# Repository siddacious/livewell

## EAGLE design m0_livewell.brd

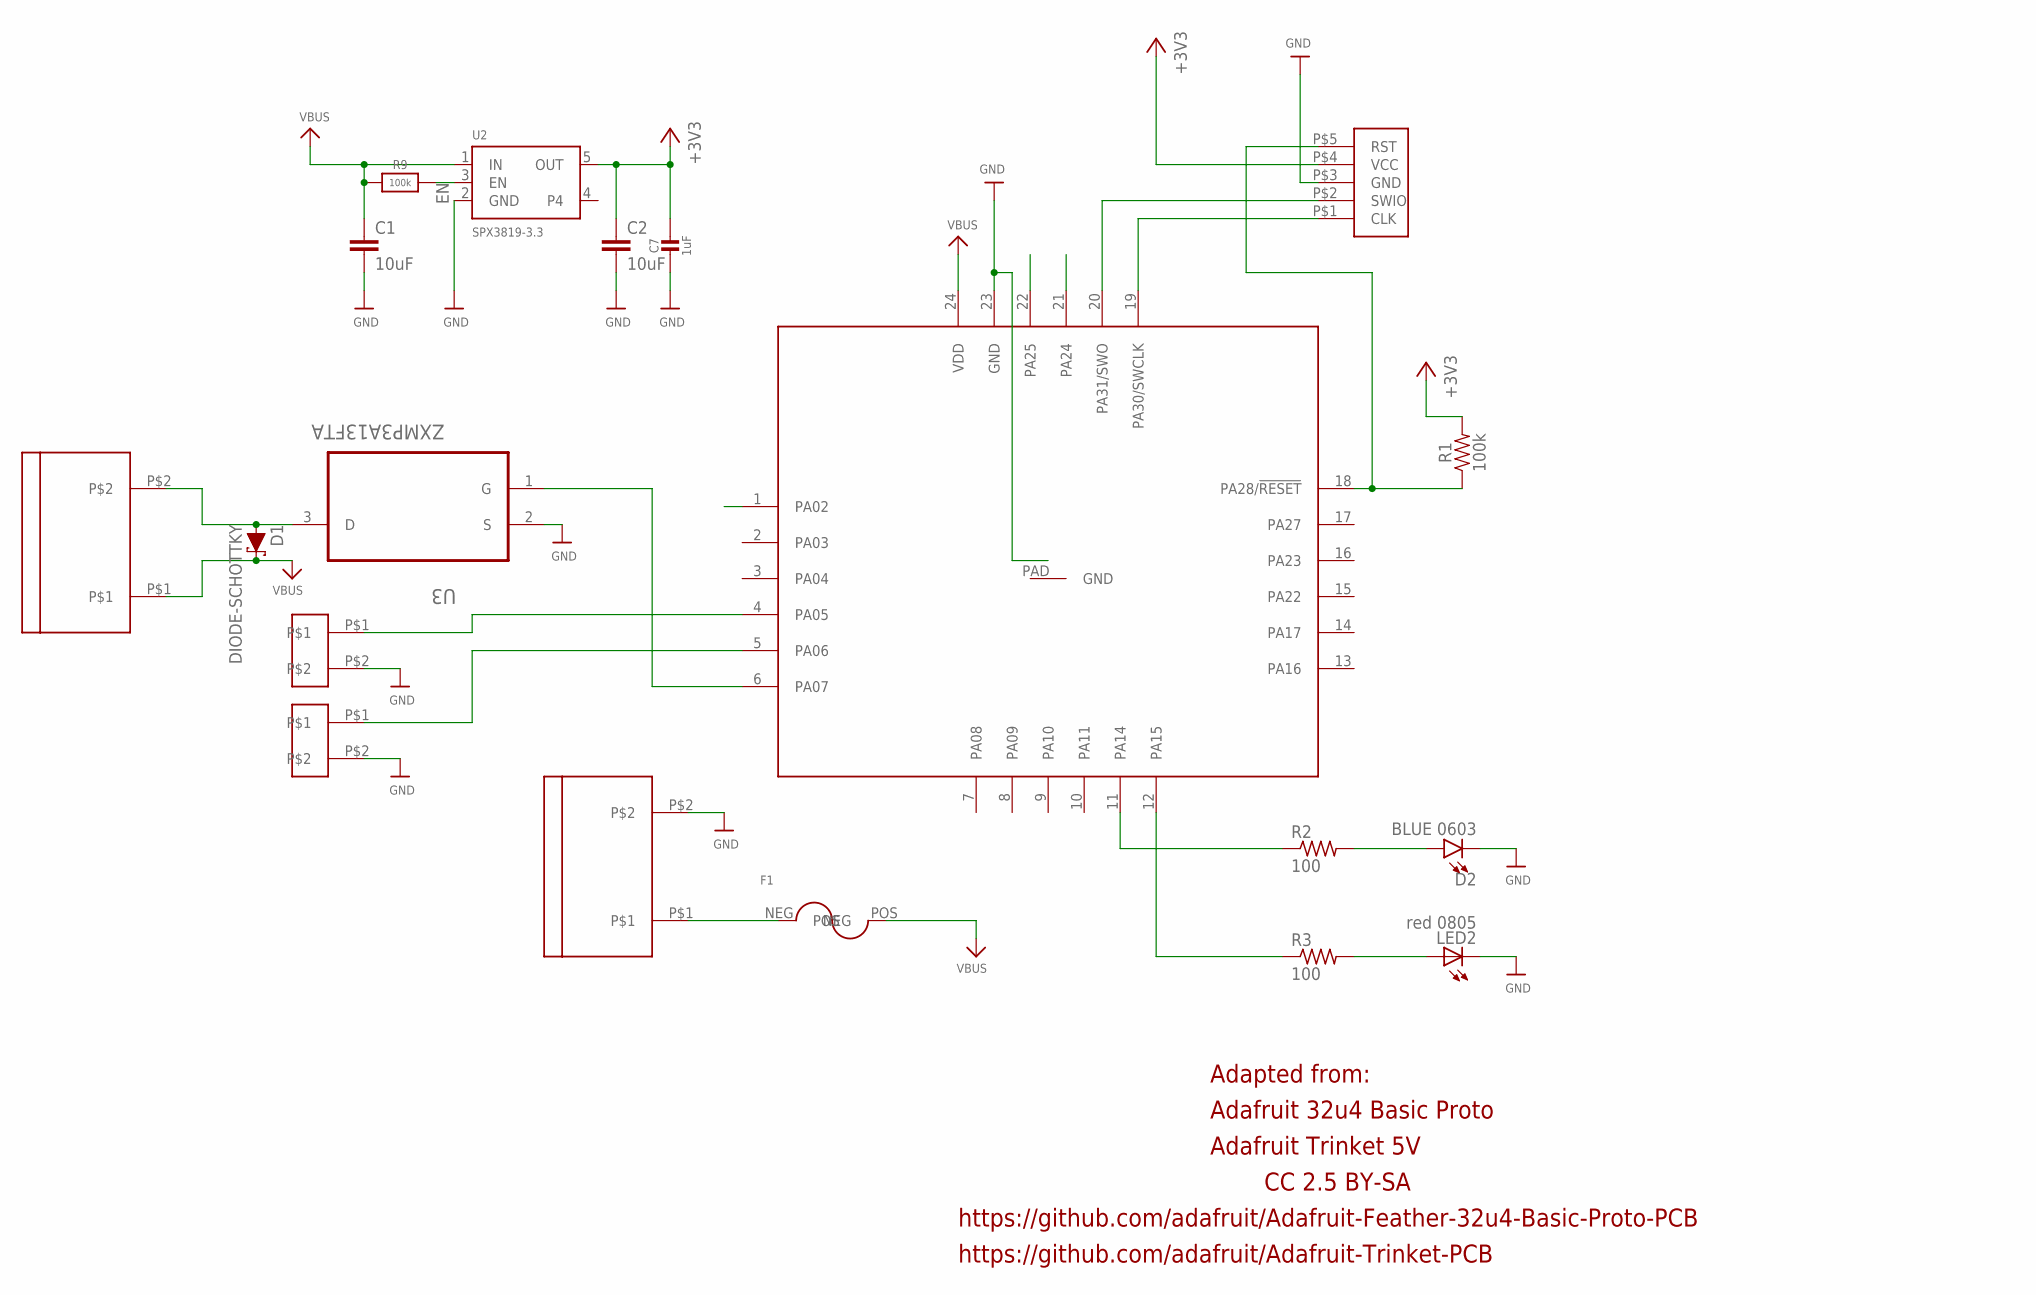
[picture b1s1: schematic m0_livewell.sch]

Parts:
C1, C2: 10uF; 0603
C7: 1uF; 0603-NO
D1: DIODE-SCHOTTKY; VISHAY_CLP1608-2L
D2: BLUE 0603; LED-0603
F1: TINYFUSE_0154003.DR
LED2: red 0805; CHIPLED_0805
R1: 100k; 0603
R2, R3: 100; R0603
R9: 100k; 0603-NO
U2: SPX3819-3.3; SOT23-5
U3: ZXMP3A13FTA; SOT95P237X112-3N
U$1: SAMD11D14A-MSAMD11D14A-M; QFN24
U$13, U$14: SCREWTERM
U$15, U$16: WP_BUTTON; WATERPROOF_BUTTON
U$17: CASTILLATED_SWDIO; SWD_CASTILLATED

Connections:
+3V3: C2.1, C7.1, R1.2, U2.5 (OUT), U$1.24 (VDD), U$17.P$4 (VCC)
+14V: C1.1, D1.P$1 (C), F1.POS (NEG), R9.1, U2.1 (IN), U$13.P$1
BTN1: U$1.5 (PA06), U$16.P$1
BTN2: U$1.4 (PA05), U$15.P$1
EN: R9.2, U2.3 (EN)
GND: C1.2, C2.2, C7.2, D2.C, LED2.C, U2.2 (GND), U3.2 (S), U$1.23 (GND), U$14.P$2, U$15.P$2, U$16.P$2, U$17.P$3 (GND)
unnamed: F1.NEG (POS), U$14.P$1
unnamed: R1.1, U$1.18 (PA28/!RESET), U$17.P$5 (RST)
unnamed: D2.A, R2.2
unnamed: LED2.A, R3.2
unnamed: R2.1, U$1.11 (PA14)
unnamed: R3.1, U$1.12 (PA15)
PWM: U3.1 (G), U$1.6 (PA07)
PWM_OUT: D1.P$2 (A), U3.3 (D), U$13.P$2
SWCLK: U$1.19 (PA30/SWCLK), U$17.P$1 (CLK)
SWDIO: U$1.20 (PA31/SWO), U$17.P$2 (SWIO)
USB_DM: U$1.21 (PA24)
USB_DP: U$1.22 (PA25)

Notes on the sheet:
Adafruit Trinket 5V
CC 2.5 BY-SA
Adapted from:
Adafruit 32u4 Basic Proto
https://github.com/adafruit/Adafruit-Feather-32u4-Basic-Proto-PCB
https://github.com/adafruit/Adafruit-Trinket-PCB

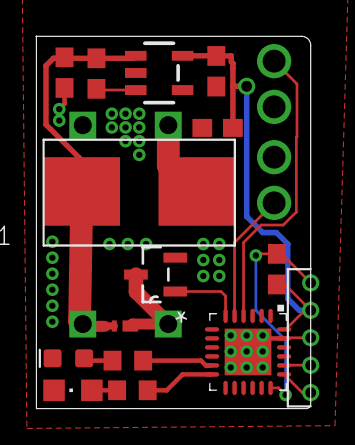
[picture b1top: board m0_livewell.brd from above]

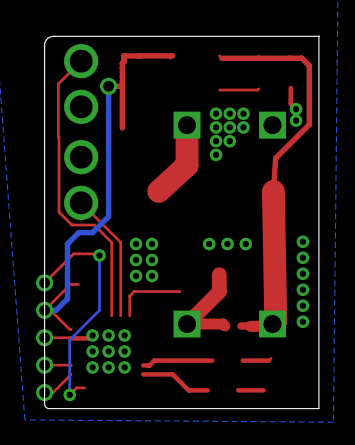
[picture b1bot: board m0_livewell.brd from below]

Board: 2 copper layers, 15.3 x 20.7 mm, 19 parts (2 on the bottom side), 16 nets.

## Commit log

2018-04-24 initial commit as send to OSHpark

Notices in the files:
parts and their libraries:
microbuilder: This work is placed in the public domain, and may be freely used for commercial and non-commercial work with the following conditions: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
SparkFun-Capacitors: Licensing: Creative Commons ShareAlike 4.0 International - https://creativecommons.org/licenses/by-sa/4.0
